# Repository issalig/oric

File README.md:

# oric
Oric computer retrothings

- oric_comp_video: PCB that gets composite video from RGBS. It uses the same size of RF module.

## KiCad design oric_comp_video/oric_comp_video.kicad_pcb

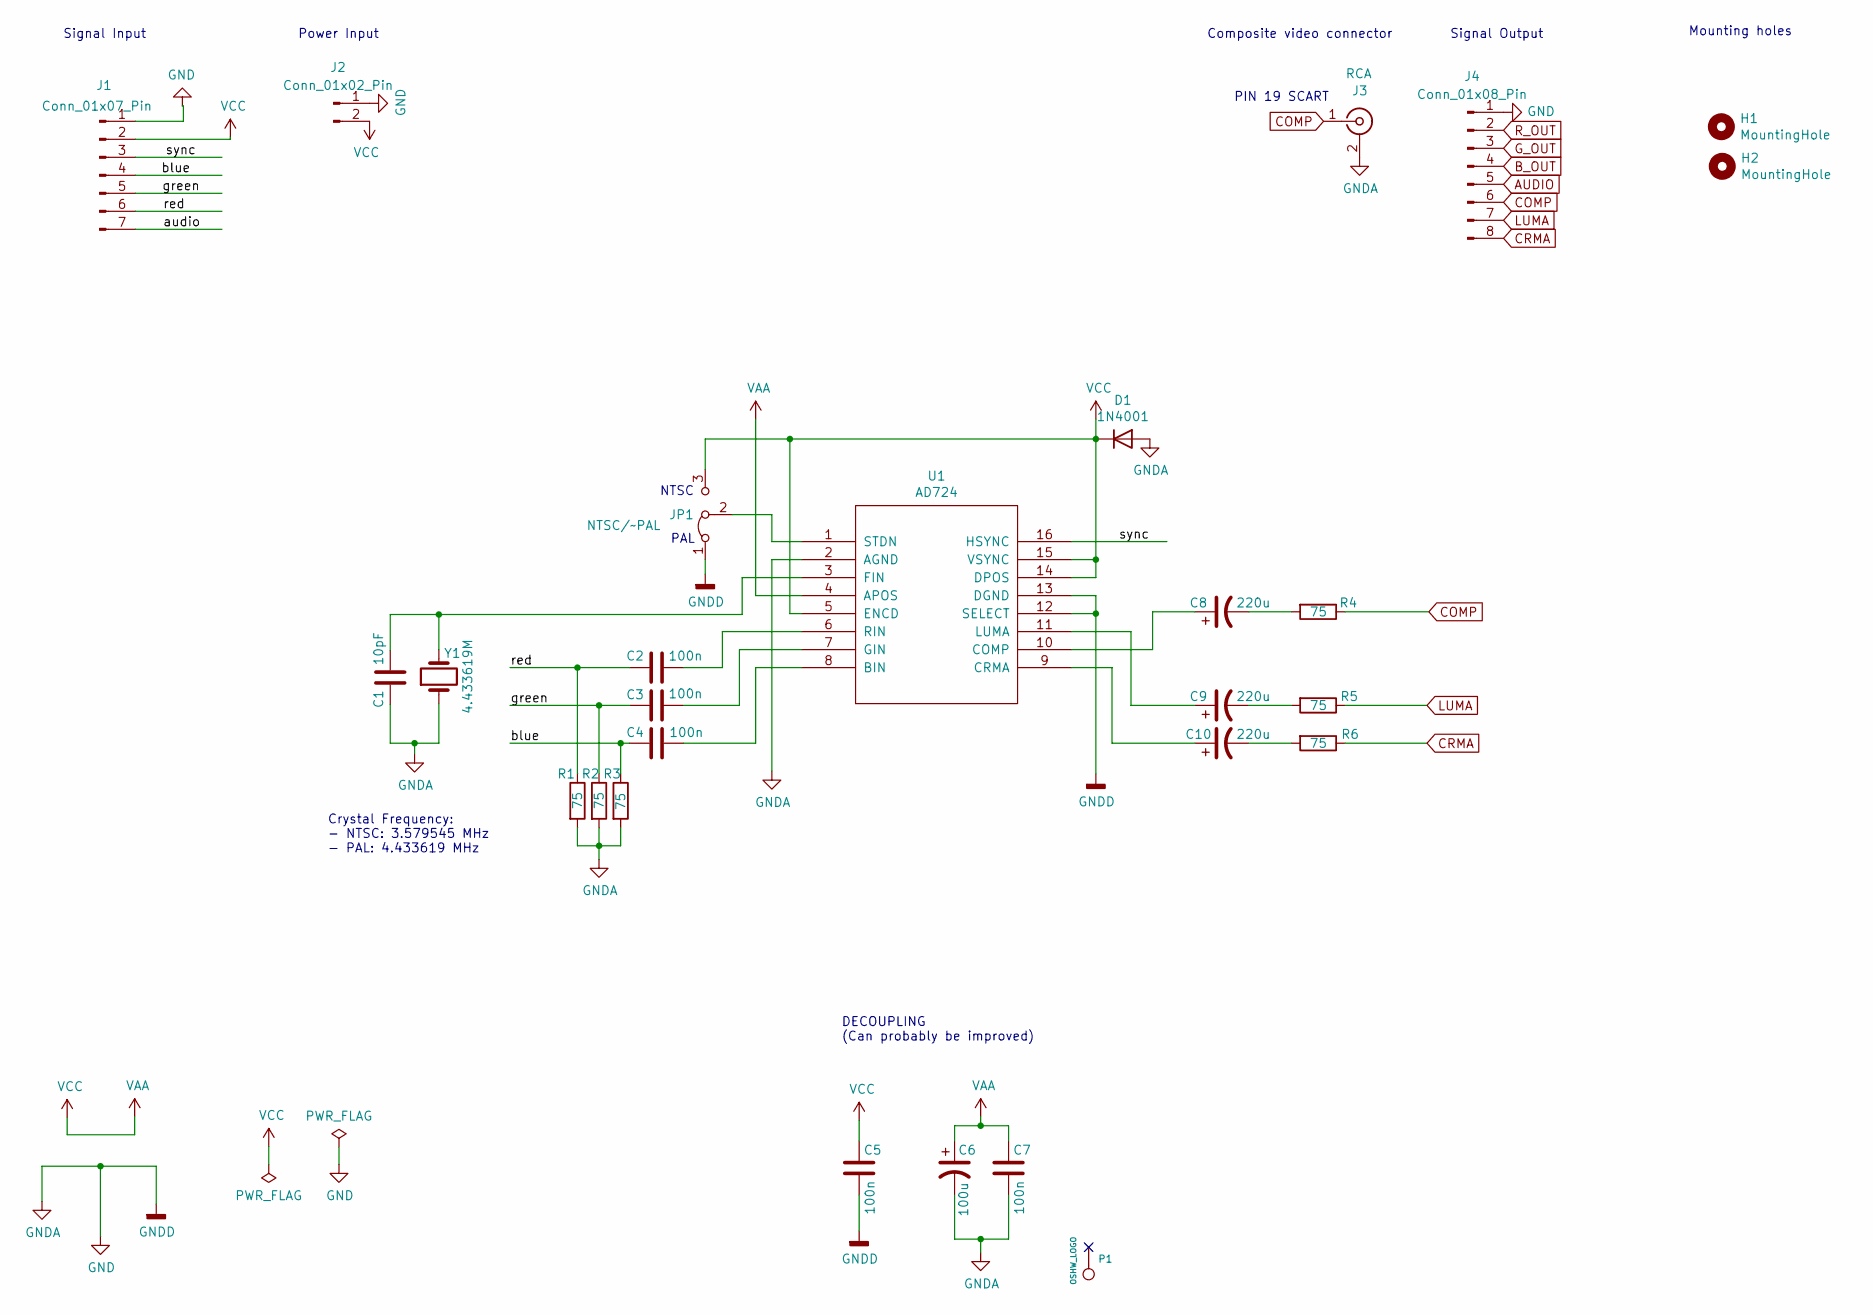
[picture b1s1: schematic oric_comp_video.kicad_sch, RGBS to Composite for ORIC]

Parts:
C1: 10pF; C_0805_2012Metric_Pad1.18x1.45mm_HandSolder
C2, C3, C4, C5, C7: 100n; C_0805_2012Metric_Pad1.18x1.45mm_HandSolder
C6: 100u; CP_Radial_D5.0mm_P2.00mm
C8, C9, C10: 220u; CP_Radial_D5.0mm_P2.00mm
D1: 1N4001; D_SMA
H1, H2: MountingHole; MountingHole_2.2mm_M2_ISO7380_Pad
J1: Conn_01x07_Pin; PinHeader_1x07_P2.54mm_Vertical
J2: Conn_01x02_Pin; PinHeader_1x02_P2.54mm_Vertical
J3: RCA; CUI_RCJ-044
J4: Conn_01x08_Pin; PinHeader_1x08_P2.54mm_Vertical
JP1: NTSC/~PAL; SolderJumper-3_P1.3mm_Bridged12_RoundedPad1.0x1.5mm
P1: OSHW_LOGO; OSHW-Logo2_7.3x6mm_Copper
R1, R2, R3, R4, R5, R6: 75; R_0805_2012Metric_Pad1.20x1.40mm_HandSolder
U1: AD724; SOIC-16W_7.5x10.3mm_P1.27mm
Y1: 4.433619M; Crystal_HC49-4H_Vertical

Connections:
/blue_in: C4.2, J1.4, R3.1
/green_in: C3.2, J1.5, R2.1
/red_in: C2.2, J1.6, R1.1
/sync_in: J1.3, U1.16 (HSYNC)
COMP: J3.1 (In), J4.6, R4.1; also elsewhere on the board
CRMA: J4.8, R6.1; also elsewhere on the board
GND: C1.2, C5.1, C6.2, C7.1, D1.2 (A), J1.1, J2.1, J3.2 (Ext), J4.1, JP1.1 (A), R1.2, R2.2, R3.2, U1.2 (AGND), U1.12 (SELECT), U1.13 (DGND), Y1.1; also elsewhere on the board
LUMA: J4.7, R5.1; also elsewhere on the board
unnamed: C8.2, R4.2
unnamed: C9.2, R5.2
unnamed: C10.2, R6.2
unnamed: JP1.2 (C), U1.1 (STDN)
unnamed: C4.1, U1.8 (BIN)
unnamed: C8.1, U1.10 (COMP)
unnamed: C10.1, U1.9 (CRMA)
unnamed: C1.1, U1.3 (FIN), Y1.2
unnamed: C3.1, U1.7 (GIN)
unnamed: C9.1, U1.11 (LUMA)
unnamed: C2.1, U1.6 (RIN)
VAA: C5.2, C6.1, C7.2, D1.1 (K), J1.2, J2.2, JP1.3 (B), U1.4 (APOS), U1.5 (ENCD), U1.14 (DPOS), U1.15 (VSYNC)

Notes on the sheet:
Crystal Frequency: - NTSC: 3.579545 MHz - PAL: 4.433619 MHz
Mounting holes
PAL
Composite video connector
Signal Input
NTSC
Power Input
Signal Output
DECOUPLING (Can probably be improved)
PIN 19 SCART

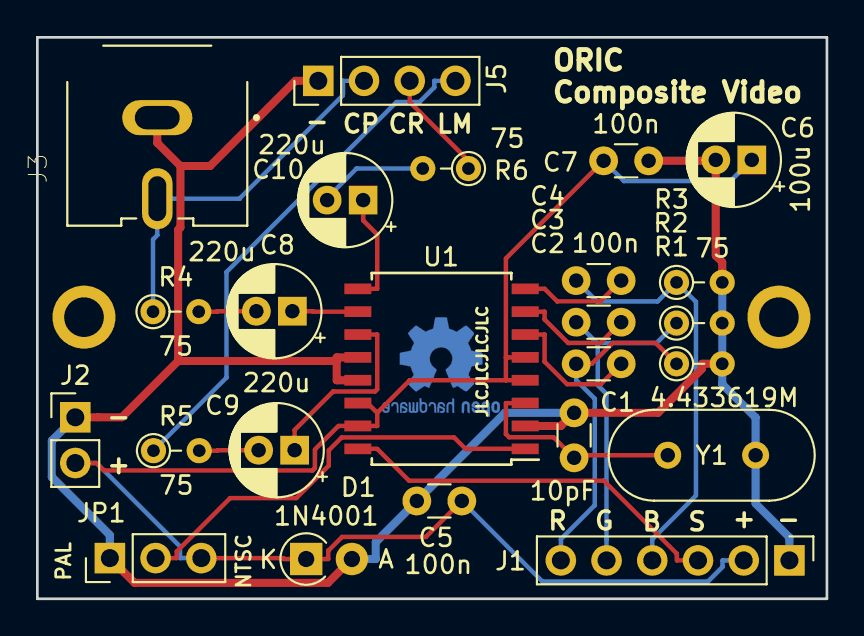
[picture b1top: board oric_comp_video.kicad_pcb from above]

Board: 2 copper layers, 43.9 x 31.2 mm, 27 parts (1 on the bottom side), 20 nets.

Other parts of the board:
J5: Conn_01x04_Male; PinHeader_1x04_P2.54mm_Vertical

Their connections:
COMP: J5.2; also elsewhere on the board
CRMA: J5.3; also elsewhere on the board
GND: J5.1; also elsewhere on the board
LUMA: J5.4; also elsewhere on the board

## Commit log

2024-04-21 Oric composite video
2024-04-21 Oric composite video board to replace RF module
2024-04-21 cleaning

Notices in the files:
oric_comp_video/oric_comp_video.kicad_pcb:
Licensed under CERN OHL v.1.2
